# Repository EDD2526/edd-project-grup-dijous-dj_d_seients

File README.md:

View this project on [CADLAB.io](https://cadlab.io/project/30198). 

# Projecte Grup D (Dijous-tarda): Seients

>**Autors:
- Joan Martínez [@JoaanMG]
- Manel Frías [@manelfriass]
- Joan Heras [@jheraas]

>**Versió: V5.0 (final)

----------

## Objectiu

En primer lloc cal explicar que estem davant de l'elaboració d’un mòdul crític per a la seguretat i el funcionament del vehicle. El sistema de SEIENTS DIGITALS és la interfície entre l'energia del cotxe i la seguretat del conductor.
Per tant ens basarem en aquests puts adjuntats al guió:

  a) 3 motors (posició, alçada, reclinació) amb els seus finals de carrera.
  b) Calefacció del seient. 
  c) Sensor digital de cinturons.
  d) Memòria externa no volàtil per guardar posicions pre-programades.

>PCB per ...

L'objectiu principal és dissenyar i fabricar una PCB funcional per a la gestió del subsistema de seients elèctrics d'un vehicle, complint els següents punts:

- Controlar 3 motors del seient:
- Posició longitudinal, alçada, Inclinació del respatller
- Detectar finals de carrera per evitar sobrecàrregues mecàniques.
- Implementar calefacció del seient amb control electrònic.
- Detectar estat del cinturó de seguretat.
- Guardar i recuperar posicions programades del seient mitjançant memòria no volàtil.
- Permetre la interacció de l’usuari amb botonera.
- Comunicar-se amb la xarxa del vehicle via bus CAN.
- Permetre monitorització i debug via USART.

## Diagrama de blocs

### Descripció/funcionalitat de cada bloc

  - ALIMENTACIÓ: El sistema s’alimenta a partir de la bateria del vehicle (12V). Aquesta tensió es condiciona mitjançant dues etapes. Això permet alimentar:

    * Microcontrolador.
    * Sensors.
    * Comunicacions.
 
  - UART: per debug i monitorització.

  - MICROCONTROLADOR: És el nucli del sistema, encarregat de: Processar les entrades (botons i sensors), controlar els motors, gestionar la comunicació amb altres mòduls. També gestiona diferents interfícies:

    * GPIO → botonera i sensors.
    * PWM → control de motors i calefacció.
    * I2C → memòria i sensor de temperatura.
    * CAN → comunicació amb el vehicle.
    * UART → debug.

  - BOTONERA: Permet a l’usuari controlar el seient:

    * Posició.
    * Alçada.
    * Reclinació.
    
  - SENSORS: de temperatura i cinturons.

  - SISTEMA DE MOTORS.

  - SISTEMA DE CALEFACCIÓ.

  - MEMÒRIA.

  - COMUNICACIÓNS.

-----------

## Requisits / Especificacions

  * Alimentació; 12V, regulada 5V
  * Microcontrolador PIC18xxxxxxxxx
  * ...

-----------

## Components

| Descripci&#243; | Ref | Package |Datasheet | Prove&#239;dor | Value | Preu | Unitats |

| Capacitor | KAF21BR71H104JM | SMD | [Enllaç](https://www.mouser.com/datasheet/3/5926/1/AutoMLCCKAF.pdf) | 100 nF| 0,078 € | x21 |

| Capacitor | KAF21BR71H104JM | SMD | [Enllaç](https://www.mouser.com/datasheet/3/5926/1/AutoMLCCKAF.pdf) | 220 uF| 0,078 € | x2 |

| Capacitor | KAF21BR71H104JM | SMD | [Enllaç](https://www.mouser.com/datasheet/3/5926/1/AutoMLCCKAF.pdf) | 10 uF| 0,078 € | x2 |

| Capacitor | KAF21BR71H104JM | THT | [Enllaç](https://www.mouser.com/datasheet/3/5926/1/AutoMLCCKAF.pdf) | 100 nF| 0,078 € | x2 |

| Capacitor | KAF21BR71H104JM | THT | [Enllaç](https://www.mouser.com/datasheet/3/5926/1/AutoMLCCKAF.pdf) | 100 nF| 0,078 € | x2 |

| Capacitor | KAF21BR71H104JM | SMD | [Enllaç](https://www.mouser.com/datasheet/3/5926/1/AutoMLCCKAF.pdf) | 0.1 uF| 0,078 € | x3 |

| --- | --- | --- | --- | ---| --- | --- |

| Exemple | XYZ1234 | SOT-23 | [Enllaç](https://...) | DigiKey | 2 |

 | Microcontrolador | PIC18F26Q83-I/SS | SOIC-28 |[Datasheet](https://www.mouser.es/datasheet/2/268/PIC18F27_47_57Q83_Preliminary_Data_Sheet_40002265B-2887591.pdf) | [Mouser](https://www.mouser.es/c/?q=PIC18F27Q83-I%2FSO)| 2,17&euro;| 1x |
| XTAL-Ressonador | CSTCR7M99G53-R0 | SMD |[Datasheet](https://www.mouser.es/datasheet/2/281/p16e-522700.pdf) | [Mouser](https://www.mouser.es/ProductDetail/Murata-Electronics/CSTCR7M99G53-R0?qs=Zd9RUO93%2Fo7cnwzsujIkpA%3D%3D)  | 0,27&euro; | 1x |

-----------

## Software

### Eines:

  * KiCad 9.0 o superior
  * 

### Configuraci&#243; :

  * 

### Funcionalitats:

  - Controlar 3 motors del seient:
  - Posició longitudinal, alçada, Inclinació del respatller
  - Detectar finals de carrera per evitar sobrecàrregues mecàniques.
  - Implementar calefacció del seient amb control electrònic.
  - Detectar estat del cinturó de seguretat.
  - Guardar i recuperar posicions programades del seient mitjançant memòria no volàtil.
  - Permetre la interacció de l’usuari amb botonera.
  - Comunicar-se amb la xarxa del vehicle via bus CAN.
  - Permetre monitorització i debug via USART

-----------

## Historial de canvis:

23/03/2026 a les 14:07
Al dia d'avui s'ha modificat el diagrama de blocs: hem ajustat petites coses per finalitzar el diagrama de blocs definitiu.

23/03/2026 a les 17:22
Tan bon punt hem modificat el digrama de blocs, al dia d'avui també s'ha modificat la part sensors: hem incorporat l'esquemàtic preliminar una vegada ajustat el diagrama de blocs. Incorporats el TMP102 (sensor de temperatura) i el Hall A3144 (sensor digital dels cinturons).

24/03/2026 a les 14:07
Al dia d'avui s'ha modificat la part d'alimentació: hem incorporat dues coses importants: FUSIBLE i DIODES TVS. Hem modificat els possibles errors mitjançant una escombrada de l'ERC. Alimentació (ACABAT AL 100%).

24/03/2026 a les 18:48
S'ha modificat la part de SENSORS: una vegada incorporats el TMP102 (sensor de temperatura) i el Hall A3144 (sensor digital dels cinturons) hem realitzat la incorporación dels components: resistències pull-up, capacitats de desacoblament, ...

25/03/2026 a les 09:35
Al dia d'avui s'ha modificat la part de sensors: hem incorporat etiquetes i hem modificat algunes connexions degut a problemes amb l'ERC, SENSORS (ACABAT AL 100%).

25/03/2026 a les 1O:07
S'ha modificat la part de SENSORS: hem finalitzat tot l'esquemàtic d'aquesta part i donem per acabada la part de SENSORS.

25/03/2026 a les 09:35
Efectuada la simulació per demostrar el funcionamenten del LM1117-3.3 (part d'ALIMENTACIÓ) a LTSpice.

| Data | Autor     | Branch | Versi&#243; | Descripci&#243; |
| --- | --- | --- | --- | --- |
|  28/03/2023 | mlopez | Master | initial commit | Primera versi&#243; d'esquem&#224;tic i selecci&#243; de components |
E s t a   e s   u n a   l   n e a   d e   p r u e b a   p a r a   e l   r e p o s i t o r i o

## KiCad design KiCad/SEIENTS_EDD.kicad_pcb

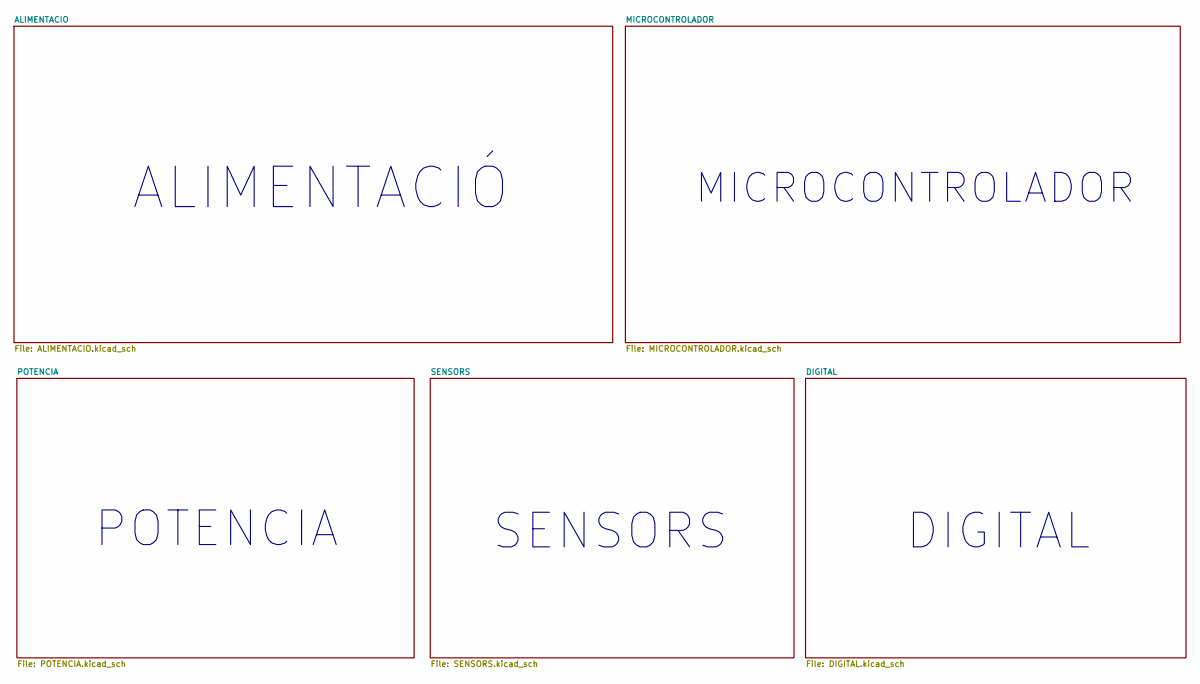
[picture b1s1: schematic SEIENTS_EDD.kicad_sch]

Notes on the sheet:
SENSORS
DIGITAL
POTENCIA
ALIMENTACIÓ
MICROCONTROLADOR

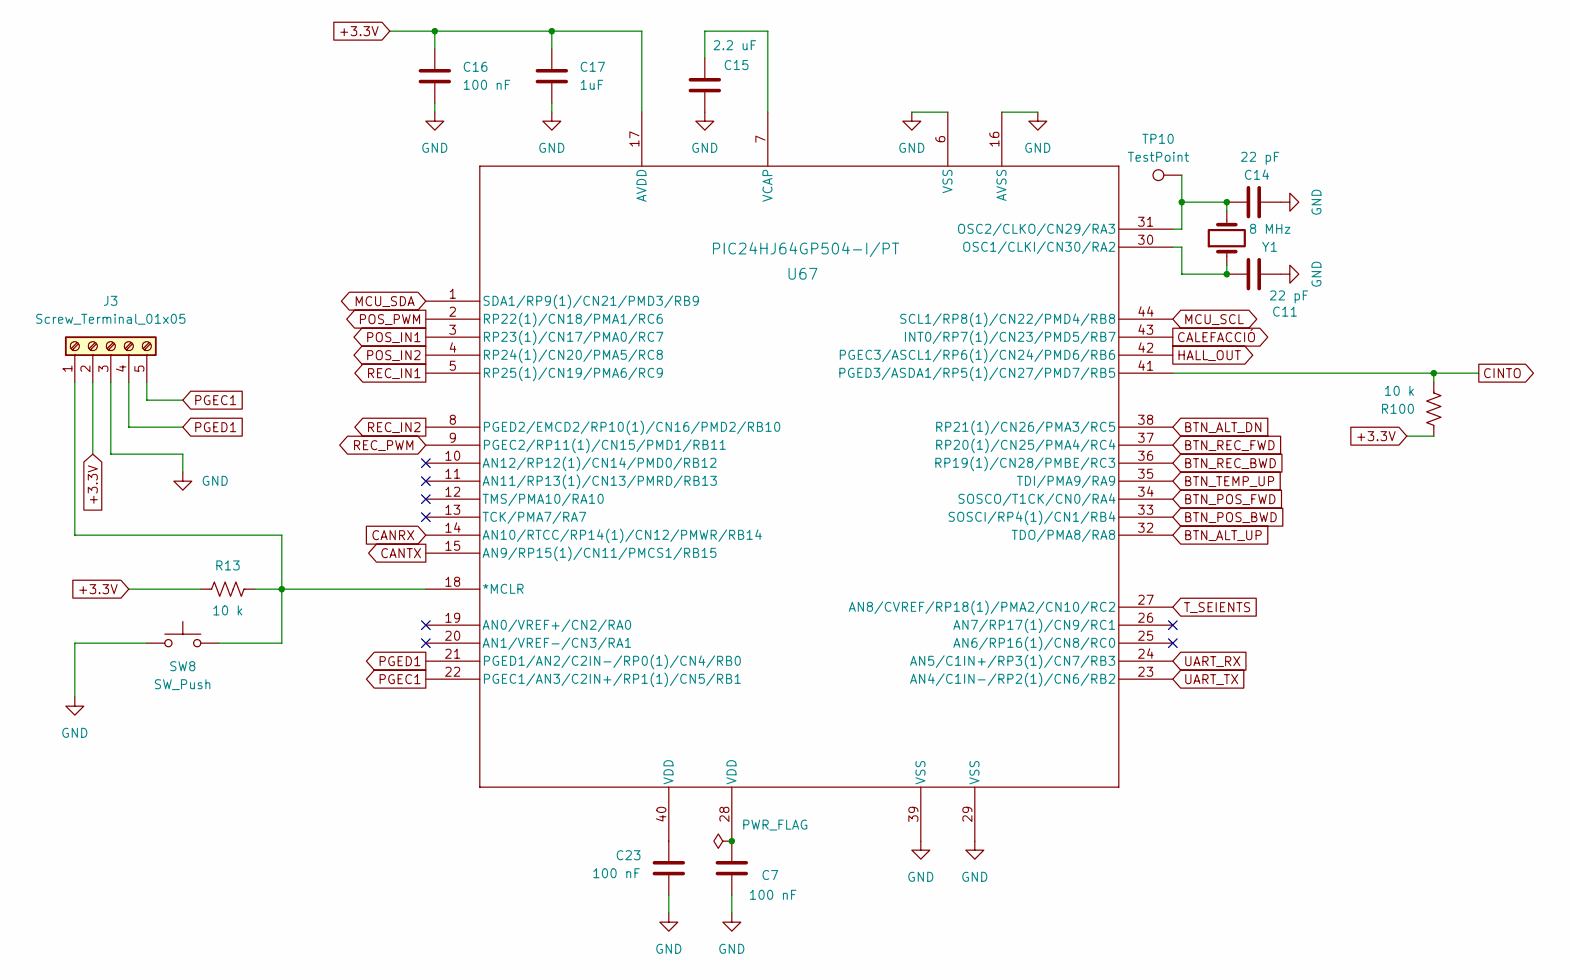
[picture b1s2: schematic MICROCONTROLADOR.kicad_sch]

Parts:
C7, C16, C23: 100 nF; C_0805_2012Metric
C11, C14: 22 pF; C_0805_2012Metric
C15: 2.2 uF; C_0805_2012Metric
C17: 1uF; C_0805_2012Metric
J3: Screw_Terminal_01x05; TerminalBlock_Phoenix_MKDS-1,5-5-5.08_1x05_P5.08mm_Horizont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
R13, R100: 10 k; R_0805_2012Metric
SW8: SW_Push; SW_Push_SPST_NO_Alps_SKRK
TP10: TestPoint; TestPoint_Pad_D1.0mm
U67: PIC24HJ64GP504-I/PT; TQFP44_10x10MC_MCH-L
Y1: 8 MHz; Crystal_HC49-4H_Vertical

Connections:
+3.3V: C16.1, C17.1, J3.2, R13.1, R100.2, U67.17 (AVDD); also elsewhere on the board
BTN_ALT_DN: U67.38 (RP21(1)/CN26/PMA3/RC5); also elsewhere on the board
BTN_ALT_UP: U67.32 (TDO/PMA8/RA8); also elsewhere on the board
BTN_POS_BWD: U67.33 (SOSCI/RP4(1)/CN1/RB4); also elsewhere on the board
BTN_POS_FWD: U67.34 (SOSCO/T1CK/CN0/RA4); also elsewhere on the board
BTN_REC_BWD: U67.36 (RP19(1)/CN28/PMBE/RC3); also elsewhere on the board
BTN_REC_FWD: U67.37 (RP20(1)/CN25/PMA4/RC4); also elsewhere on the board
BTN_TEMP_UP: U67.35 (TDI/PMA9/RA9); also elsewhere on the board
CALEFACCIÓ: U67.43 (INT0/RP7(1)/CN23/PMD5/RB7); also elsewhere on the board
CANRX: U67.14 (AN10/RTCC/RP14(1)/CN12/PMWR/RB14); also elsewhere on the board
CANTX: U67.15 (AN9/RP15(1)/CN11/PMCS1/RB15); also elsewhere on the board
CINTO: R100.1, U67.41 (PGED3/ASDA1/RP5(1)/CN27/PMD7/RB5); also elsewhere on the board
GND: C7.2, C11.2, C14.2, C15.1, C16.2, C17.2, C23.2, J3.3, SW8.1, U67.6 (VSS), U67.16 (AVSS), U67.29 (VSS), U67.39 (VSS); also elsewhere on the board
HALL_OUT: U67.42 (PGEC3/ASCL1/RP6(1)/CN24/PMD6/RB6); also elsewhere on the board
MCU_SCL: U67.44 (SCL1/RP8(1)/CN22/PMD4/RB8); also elsewhere on the board
MCU_SDA: U67.1 (SDA1/RP9(1)/CN21/PMD3/RB9); also elsewhere on the board
unnamed: C7.1, U67.28 (VDD)
unnamed: C23.1, U67.40 (VDD)
unnamed: J3.1, R13.2, SW8.2, U67.18 (*MCLR)
unnamed: C11.1, U67.30 (OSC1/CLKI/CN30/RA2), Y1.1
unnamed: C14.1, TP10.1, U67.31 (OSC2/CLKO/CN29/RA3), Y1.2
unnamed: C15.2, U67.7 (VCAP)
PGEC1: J3.5, U67.22 (PGEC1/AN3/C2IN+/RP1(1)/CN5/RB1)
PGED1: J3.4, U67.21 (PGED1/AN2/C2IN-/RP0(1)/CN4/RB0)
POS_IN1: U67.3 (RP23(1)/CN17/PMA0/RC7); also elsewhere on the board
POS_IN2: U67.4 (RP24(1)/CN20/PMA5/RC8); also elsewhere on the board
POS_PWM: U67.2 (RP22(1)/CN18/PMA1/RC6); also elsewhere on the board
REC_IN1: U67.5 (RP25(1)/CN19/PMA6/RC9); also elsewhere on the board
REC_IN2: U67.8 (PGED2/EMCD2/RP10(1)/CN16/PMD2/RB10); also elsewhere on the board
REC_PWM: U67.9 (PGEC2/RP11(1)/CN15/PMD1/RB11); also elsewhere on the board
T_SEIENTS: U67.27 (AN8/CVREF/RP18(1)/PMA2/CN10/RC2); also elsewhere on the board
UART_RX: U67.24 (AN5/C1IN+/RP3(1)/CN7/RB3); also elsewhere on the board
UART_TX: U67.23 (AN4/C1IN-/RP2(1)/CN6/RB2); also elsewhere on the board

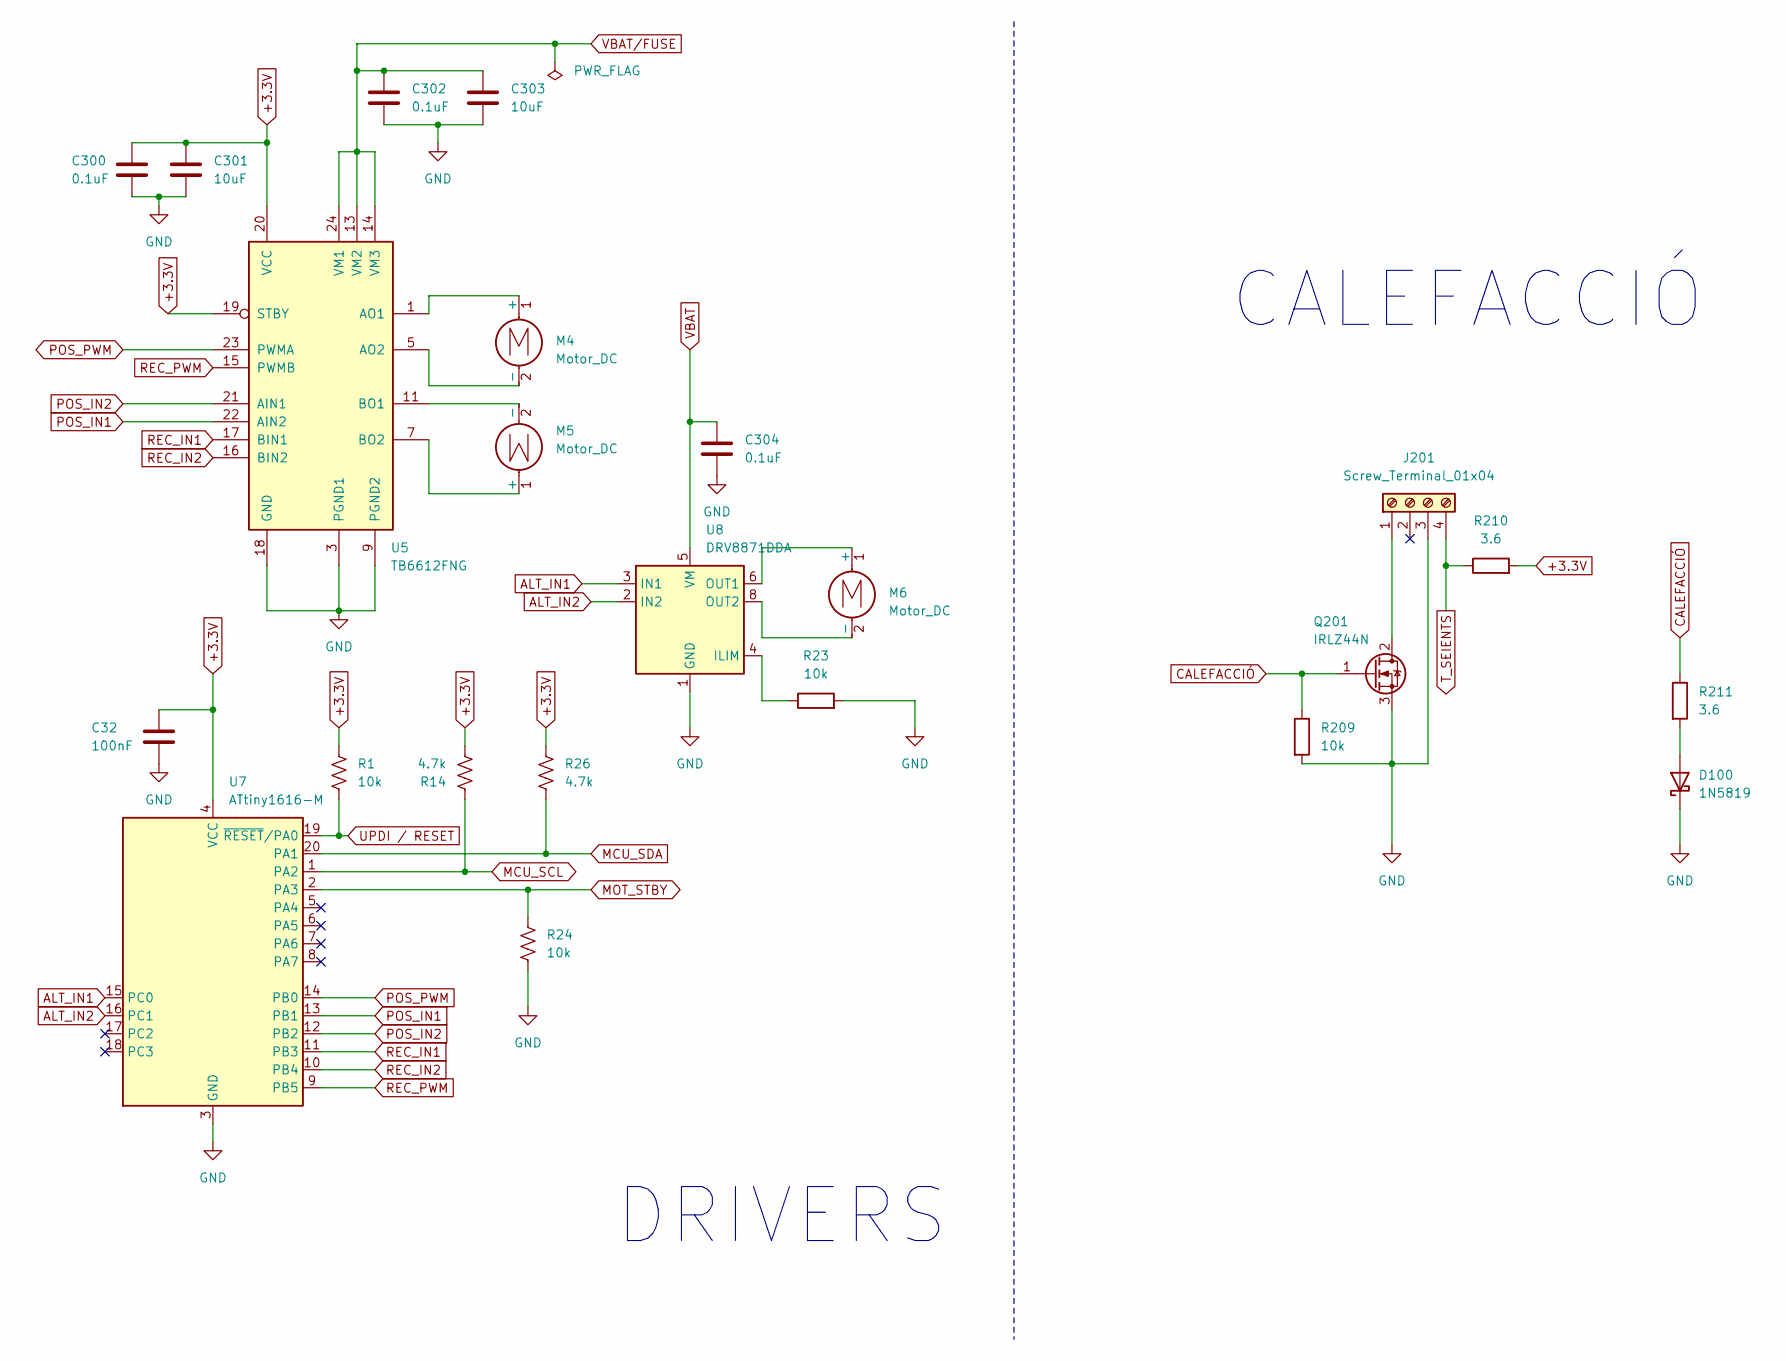
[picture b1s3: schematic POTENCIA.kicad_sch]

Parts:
C32: 100nF; C_0805_2012Metric
C300, C302, C304: 0.1uF; C_0805_2012Metric
C301, C303: 10uF; CP_Radial_D5.0mm_P2.50mm
D100: 1N5819; D_DO-41_SOD81_P10.16mm_Horizontal
J201: Screw_Terminal_01x04; TerminalBlock_Phoenix_MKDS-1,5-4-5.08_1x04_P5.08mm_Horizont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
M4, M5, M6: Motor_DC; TerminalBlock_Phoenix_MKDS-1,5-2-5.08_1x02_P5.08mm_Horizont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
Q201: IRLZ44N; TO-220-3_Vertical
R1, R23, R24, R209: 10k; R_0805_2012Metric
R14, R26: 4.7k; R_0805_2012Metric
R210, R211: 3.6; R_0805_2012Metric
U5: TB6612FNG; SSOP-24_5.3x8.2mm_P0.65mm
U7: ATtiny1616-M; VQFN-20-1EP_3x3mm_P0.4mm_EP1.7x1.7mm
U8: DRV8871DDA; Texas_HTSOP-8-1EP_3.9x4.9mm_P1.27mm_EP2.95x4.9mm_Mask2.4x3.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

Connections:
+3.3V: C32.1, C300.1, C301.1, R1.1, R14.2, R26.1, R210.2, U5.19 (STBY), U5.20 (VCC), U7.4 (VCC); also elsewhere on the board
ALT_IN1: U7.15 (PC0), U8.3 (IN1)
ALT_IN2: U7.16 (PC1), U8.2 (IN2)
CALEFACCIÓ: Q201.1 (G), R209.1, R211.1; also elsewhere on the board
GND: C32.2, C300.2, C301.2, C302.2, C303.2, C304.2, D100.1 (K), J201.3, Q201.3 (S), R23.2, R24.2, R209.2, U5.3 (PGND1), U5.4 (PGND1), U5.9 (PGND2), U5.10 (PGND2), U5.18 (GND), U7.3 (GND), U7.21 (GND), U8.1 (GND), U8.7 (GND), U8.9 (GND); also elsewhere on the board
MCU_SCL: R14.1, U7.1 (PA2); also elsewhere on the board
MCU_SDA: R26.2, U7.20 (PA1); also elsewhere on the board
MOT_STBY: R24.1, U7.2 (PA3)
unnamed: D100.2 (A), R211.2
unnamed: J201.1, Q201.2 (D)
unnamed: M4.1 (+), U5.1 (AO1), U5.2 (AO1)
unnamed: M4.2 (-), U5.5 (AO2), U5.6 (AO2)
unnamed: M5.1 (+), U5.7 (BO2), U5.8 (BO2)
unnamed: M5.2 (-), U5.11 (BO1), U5.12 (BO1)
unnamed: M6.1 (+), U8.6 (OUT1)
unnamed: M6.2 (-), U8.8 (OUT2)
unnamed: R23.1, U8.4 (ILIM)
POS_IN1: U5.22 (AIN2), U7.13 (PB1); also elsewhere on the board
POS_IN2: U5.21 (AIN1), U7.12 (PB2); also elsewhere on the board
POS_PWM: U5.23 (PWMA), U7.14 (PB0); also elsewhere on the board
REC_IN1: U5.17 (BIN1), U7.11 (PB3); also elsewhere on the board
REC_IN2: U5.16 (BIN2), U7.10 (PB4); also elsewhere on the board
REC_PWM: U5.15 (PWMB), U7.9 (PB5); also elsewhere on the board
T_SEIENTS: J201.4, R210.1; also elsewhere on the board
UPDI / RESET: R1.2, U7.19 (~RESET/PA0)
VBAT: C304.1, U8.5 (VM); also elsewhere on the board
VBAT/FUSE: C302.1, C303.1, U5.13 (VM2), U5.14 (VM3), U5.24 (VM1); also elsewhere on the board

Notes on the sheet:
CALEFACCIÓ
DRIVERS

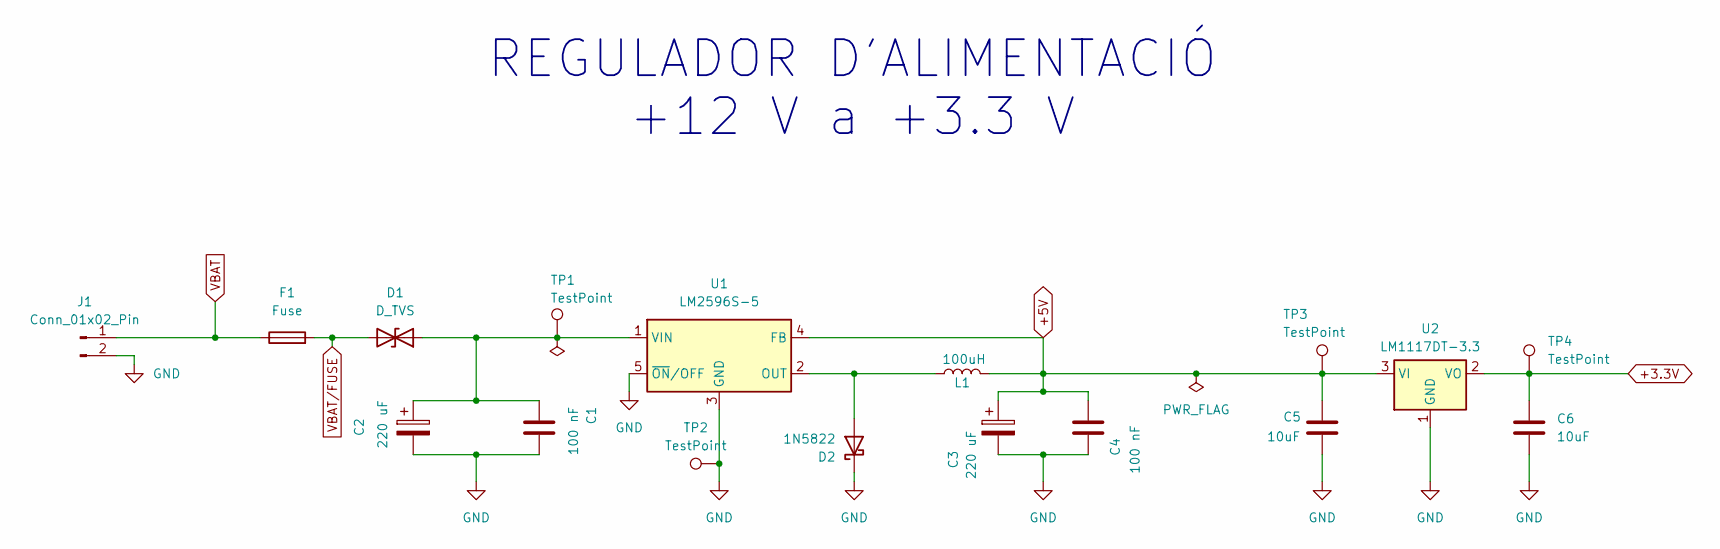
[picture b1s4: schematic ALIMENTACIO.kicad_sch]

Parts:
C1, C4: 100 nF; C_0805_2012Metric
C2, C3: 220 uF; C_0805_2012Metric
C5, C6: 10uF; C_0805_2012Metric
D1: D_TVS; D_SMA
D2: 1N5822; D_DO-201AD_P15.24mm_Horizontal
F1: Fuse; Fuseholder_Cylinder-5x20mm_Schurter_0031_8201_Horizontal_Op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
J1: Conn_01x02_Pin; TerminalBlock_Phoenix_MKDS-1,5-2-5.08_1x02_P5.08mm_Horizont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
L1: 100uH; L_Radial_D10.0mm_P5.00mm_Fastron_07M
TP1, TP2, TP3, TP4: TestPoint; TestPoint_Pad_D1.0mm
U1: LM2596S-5; TO-263-5_TabPin3
U2: LM1117DT-3.3; TO-252-3_TabPin2

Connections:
+3.3V: C6.1, TP4.1, U2.2 (VO); also elsewhere on the board
+5V: C3.1, C4.1, C5.1, L1.2, TP3.1, U1.4 (FB), U2.3 (VI); also elsewhere on the board
GND: C1.1, C2.2, C3.2, C4.2, C5.2, C6.2, D2.1 (K), J1.2, TP2.1, U1.3 (GND), U1.5 (~ON/OFF), U2.1 (GND); also elsewhere on the board
unnamed: C1.2, C2.1, D1.1 (A1), TP1.1, U1.1 (VIN)
unnamed: D2.2 (A), L1.1, U1.2 (OUT)
VBAT: F1.1, J1.1; also elsewhere on the board
VBAT/FUSE: D1.2 (A2), F1.2; also elsewhere on the board

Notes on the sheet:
REGULADOR D'ALIMENTACIÓ +12 V a +3.3 V

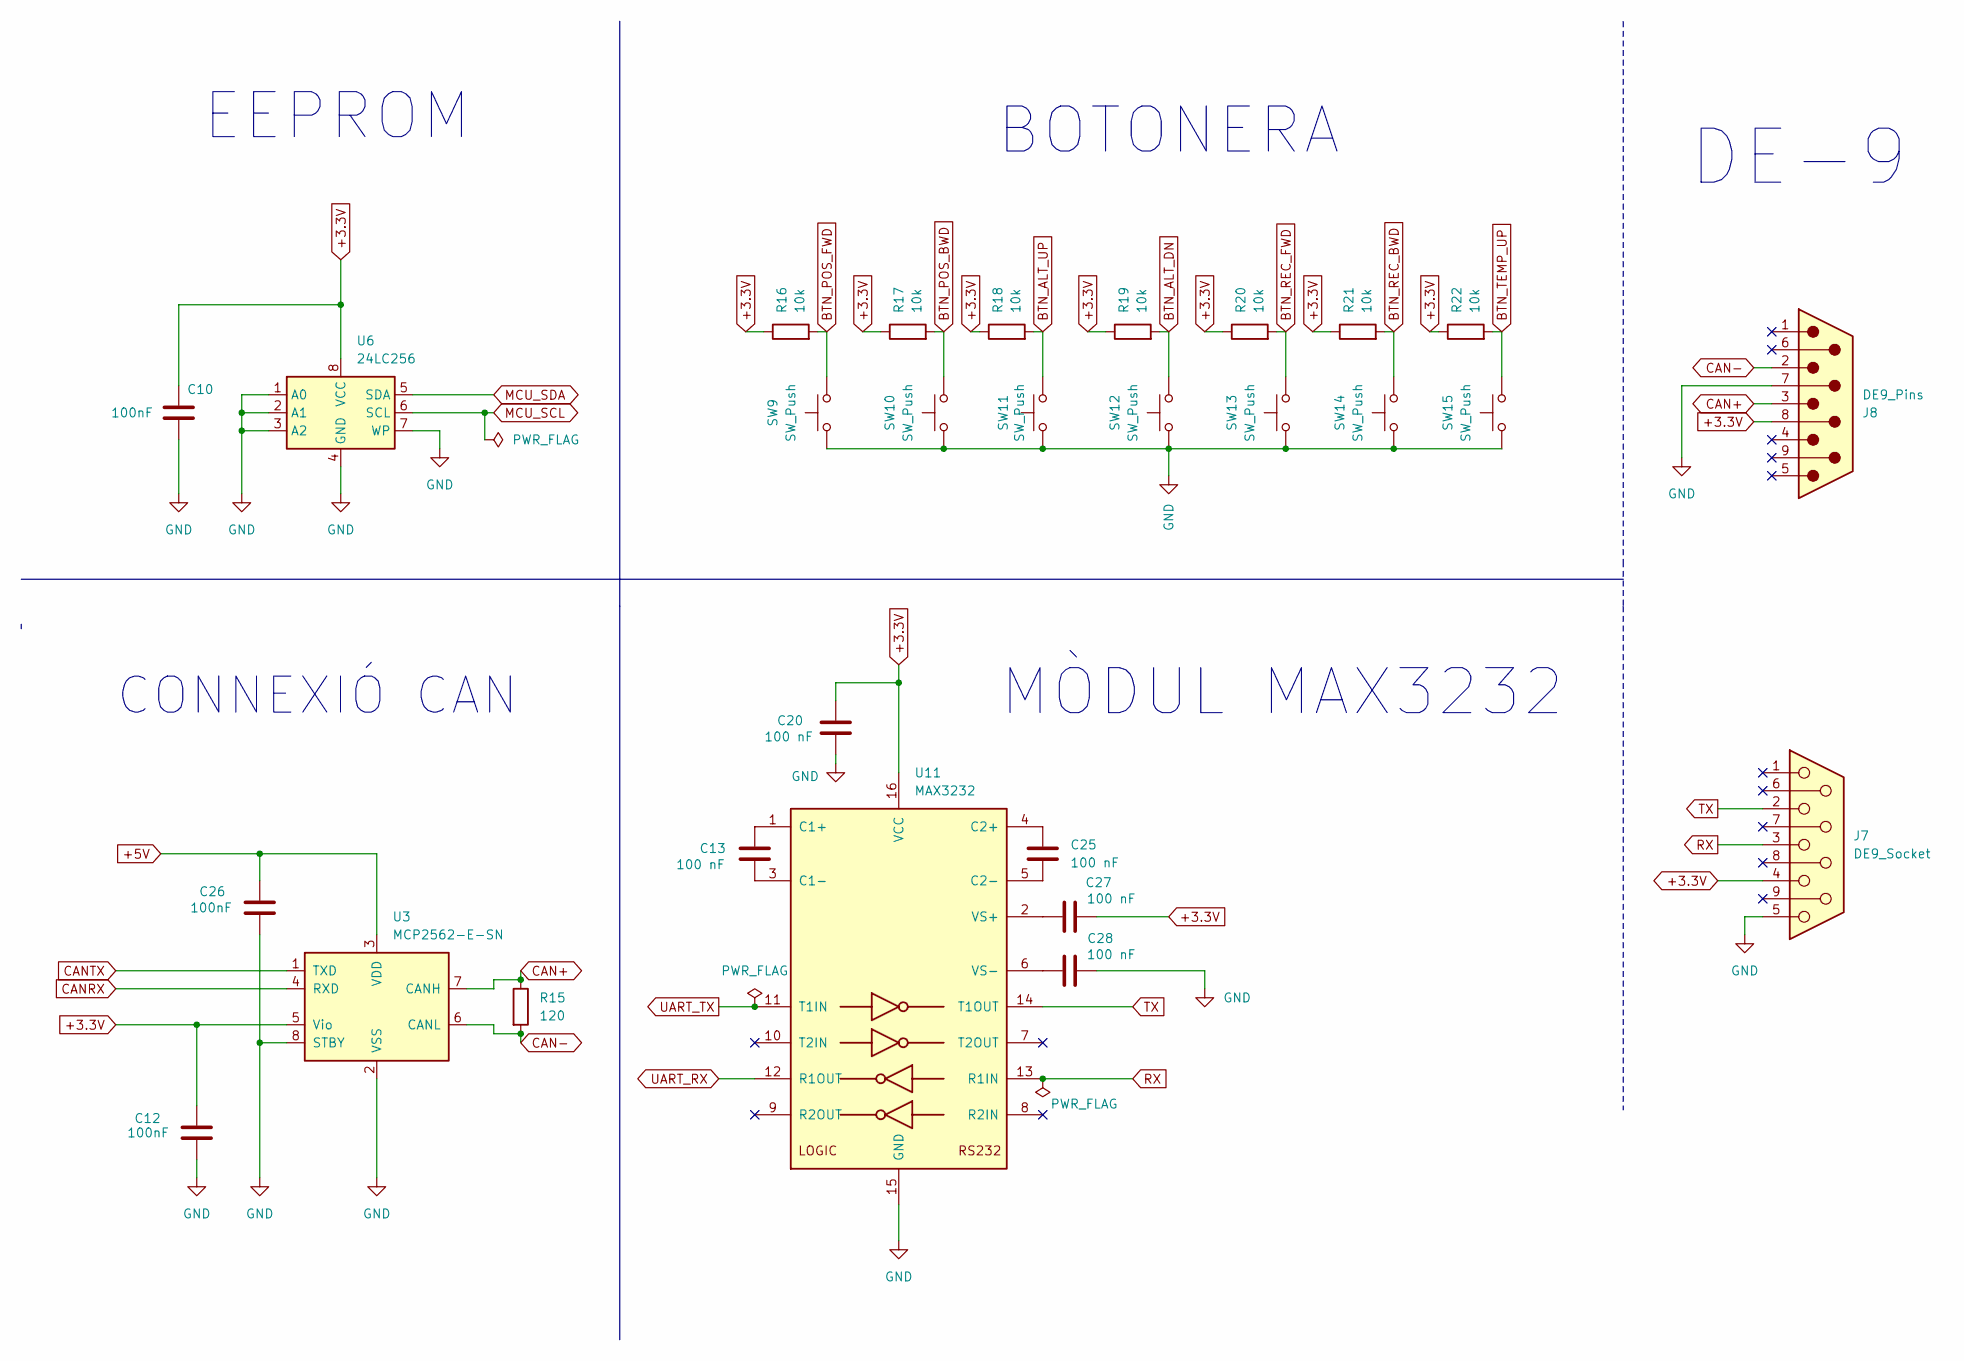
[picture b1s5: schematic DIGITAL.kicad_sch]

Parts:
C10, C12, C26: 100nF; C_0805_2012Metric
C13, C20, C25, C27, C28: 100 nF; C_0805_2012Metric
J7: DE9_Socket; DSUB-9_Socket_Horizontal_P2.77x2.84mm_EdgePinOffset4.94mm_H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
J8: DE9_Pins; DSUB-9_Pins_Horizontal_P2.77x2.84mm_EdgePinOffset4.94mm_Hou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
R15: 120; R_0805_2012Metric
R16, R17, R18, R19, R20, R21, R22: 10k; R_0805_2012Metric
SW9, SW10, SW11, SW12, SW13, SW14, SW15: SW_Push; SW_Push_SPST_NO_Alps_SKRK
U3: MCP2562-E-SN; SOIC-8_3.9x4.9mm_P1.27mm
U6: 24LC256; SOIC-8_3.9x4.9mm_P1.27mm
U11: MAX3232; SOIC-16_3.9x9.9mm_P1.27mm

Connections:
+3.3V: C10.2, C12.2, C20.1, C27.2, J7.4, J8.8, R16.1, R17.1, R18.1, R19.1, R20.1, R21.1, R22.1, U3.5 (Vio), U6.8 (VCC), U11.16 (VCC); also elsewhere on the board
+5V: C26.2, U3.3 (VDD); also elsewhere on the board
BTN_ALT_DN: R19.2, SW12.2; also elsewhere on the board
BTN_ALT_UP: R18.2, SW11.2; also elsewhere on the board
BTN_POS_BWD: R17.2, SW10.2; also elsewhere on the board
BTN_POS_FWD: R16.2, SW9.2; also elsewhere on the board
BTN_REC_BWD: R21.2, SW14.2; also elsewhere on the board
BTN_REC_FWD: R20.2, SW13.2; also elsewhere on the board
BTN_TEMP_UP: R22.2, SW15.2; also elsewhere on the board
CAN+: J8.3, R15.1, U3.7 (CANH)
CAN-: J8.2, R15.2, U3.6 (CANL)
CANRX: U3.4 (RXD); also elsewhere on the board
CANTX: U3.1 (TXD); also elsewhere on the board
GND: C10.1, C12.1, C20.2, C26.1, C28.2, J7.5, J8.7, SW9.1, SW10.1, SW11.1, SW12.1, SW13.1, SW14.1, SW15.1, U3.2 (VSS), U3.8 (STBY), U6.1 (A0), U6.2 (A1), U6.3 (A2), U6.4 (GND), U6.7 (WP), U11.15 (GND); also elsewhere on the board
MCU_SCL: U6.6 (SCL); also elsewhere on the board
MCU_SDA: U6.5 (SDA); also elsewhere on the board
unnamed: C13.1, U11.1 (C1+)
unnamed: C13.2, U11.3 (C1-)
unnamed: C25.1, U11.4 (C2+)
unnamed: C25.2, U11.5 (C2-)
unnamed: C27.1, U11.2 (VS+)
unnamed: C28.1, U11.6 (VS-)
RX: J7.3, U11.13 (R1IN)
TX: J7.2, U11.14 (T1OUT)
UART_RX: U11.12 (R1OUT); also elsewhere on the board
UART_TX: U11.11 (T1IN); also elsewhere on the board

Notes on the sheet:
BOTONERA
EEPROM
MÒDUL MAX3232
DE-9
CONNEXIÓ CAN

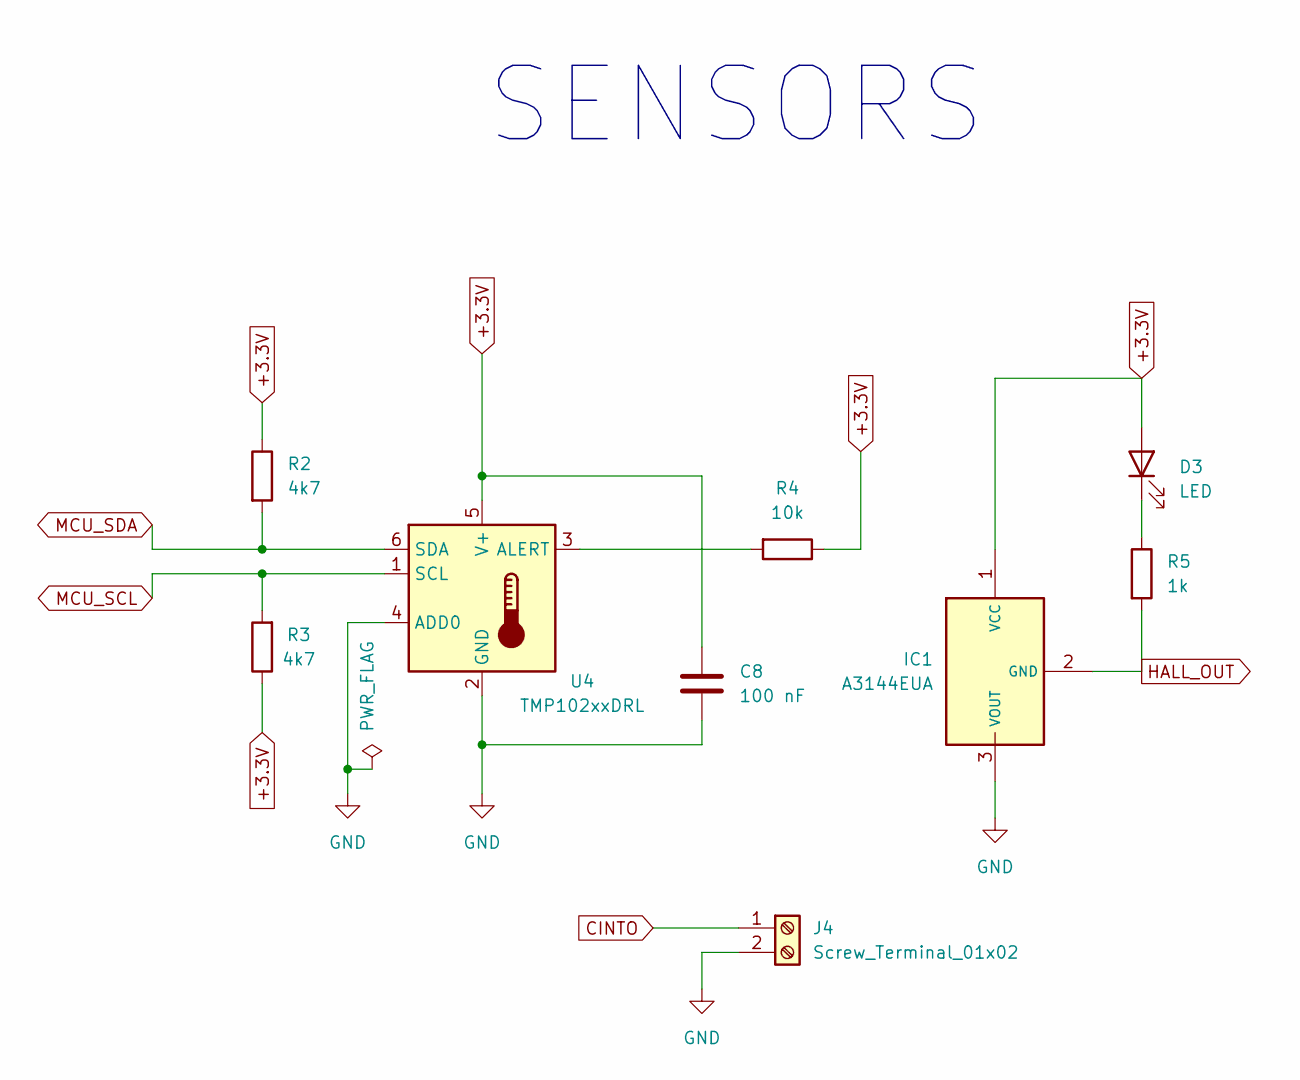
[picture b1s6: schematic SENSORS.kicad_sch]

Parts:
C8: 100 nF; C_0805_2012Metric
D3: LED; LED_D3.0mm
IC1: A3144EUA; Manufacturer_Part_Number A3144EUA
J4: Screw_Terminal_01x02; TerminalBlock_Phoenix_MKDS-1,5-2-5.08_1x02_P5.08mm_Horizont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
R2, R3: 4k7; R_0805_2012Metric
R4: 10k; R_0805_2012Metric
R5: 1k; R_0805_2012Metric
U4: TMP102xxDRL; SOT-563

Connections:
+3.3V: C8.1, D3.2 (A), IC1.1 (VCC), R2.1, R3.1, R4.1, U4.5 (V+); also elsewhere on the board
CINTO: J4.1; also elsewhere on the board
GND: C8.2, IC1.3 (VOUT), J4.2, U4.2 (GND), U4.4 (ADD0); also elsewhere on the board
HALL_OUT: IC1.2 (GND), R5.2; also elsewhere on the board
MCU_SCL: R3.2, U4.1 (SCL); also elsewhere on the board
MCU_SDA: R2.2, U4.6 (SDA); also elsewhere on the board
unnamed: D3.1 (K), R5.1
unnamed: R4.2, U4.3 (ALERT)

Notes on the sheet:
SENSORS

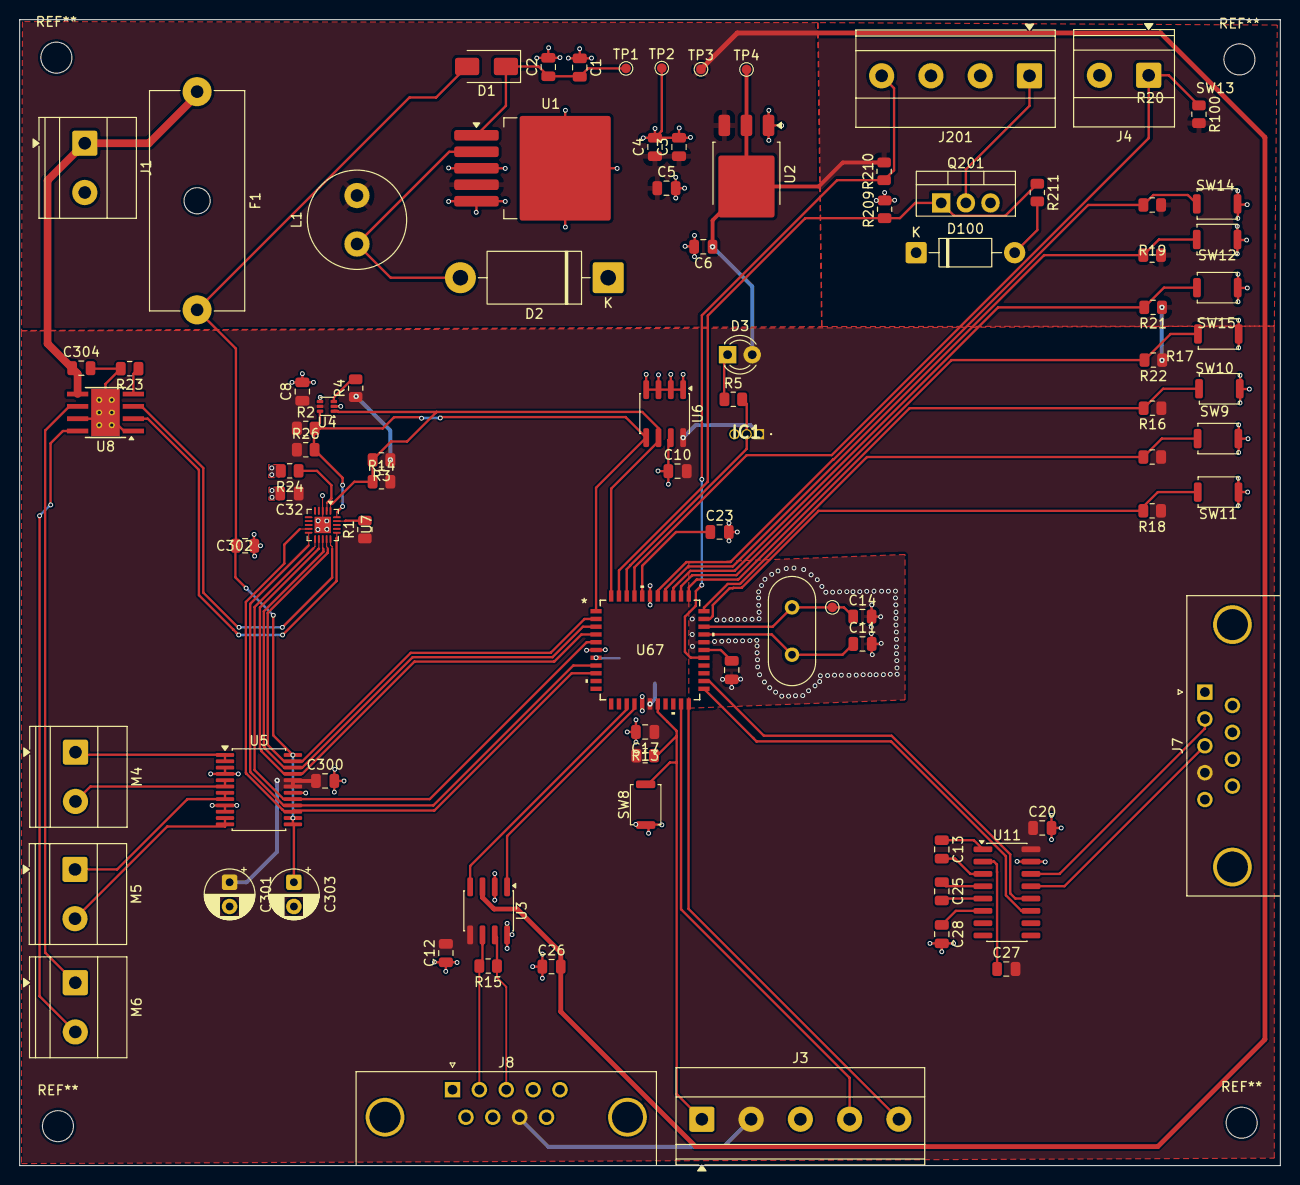
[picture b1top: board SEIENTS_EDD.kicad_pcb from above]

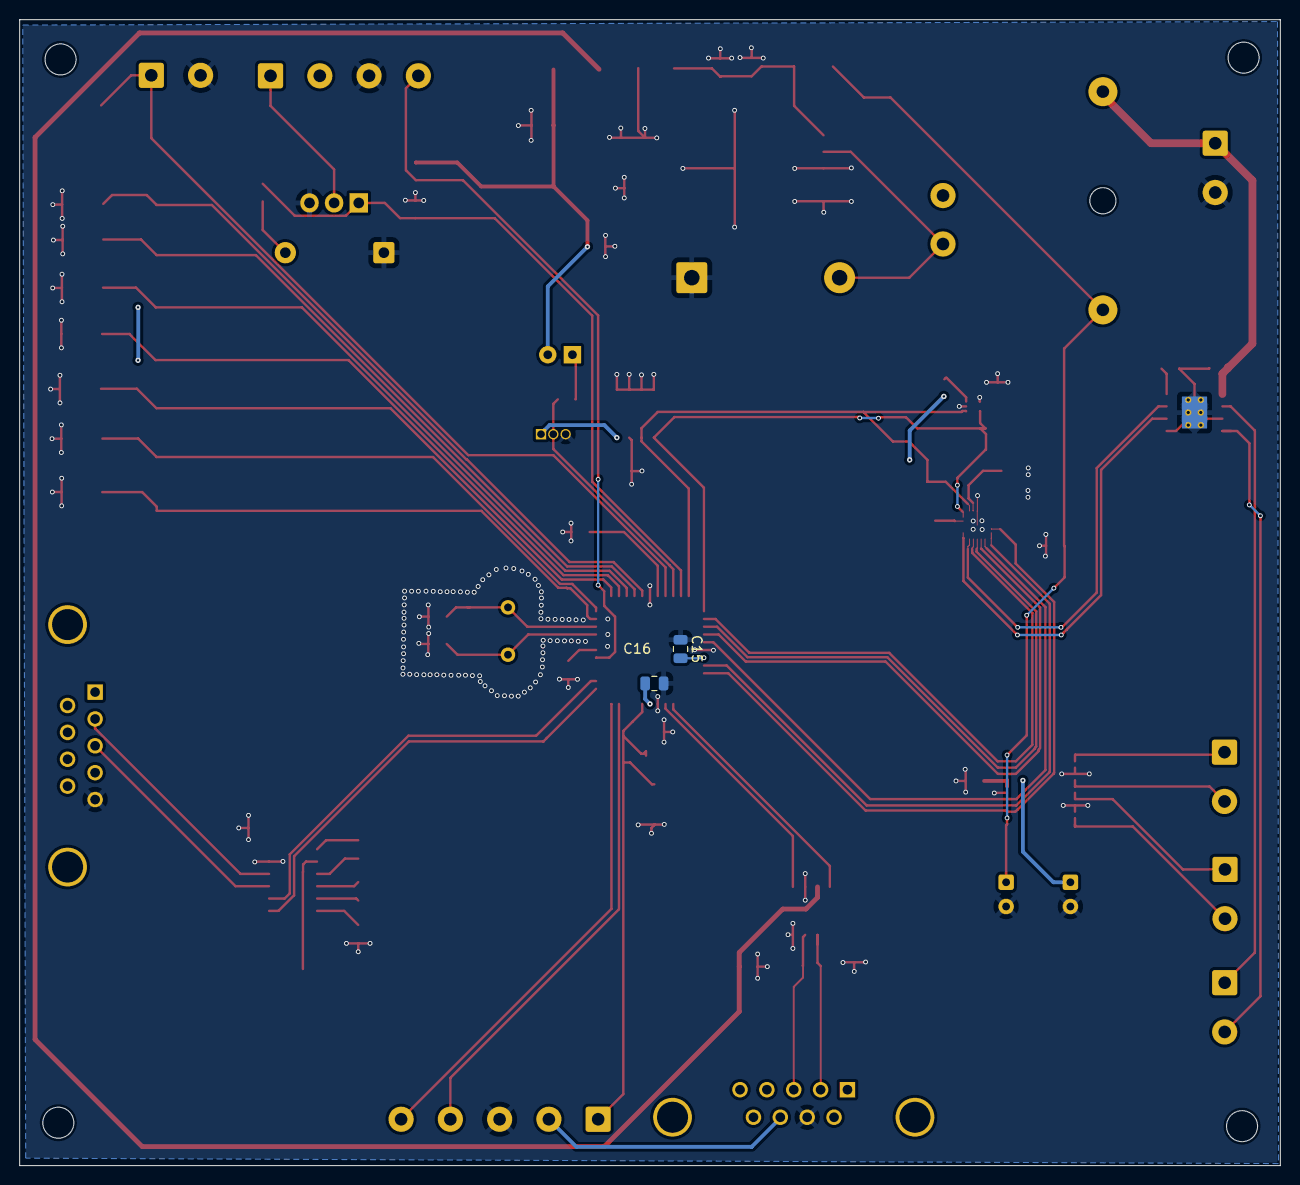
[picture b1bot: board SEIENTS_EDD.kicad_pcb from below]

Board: 2 copper layers, 130.0 x 118.2 mm, 91 parts (2 on the bottom side), 63 nets.

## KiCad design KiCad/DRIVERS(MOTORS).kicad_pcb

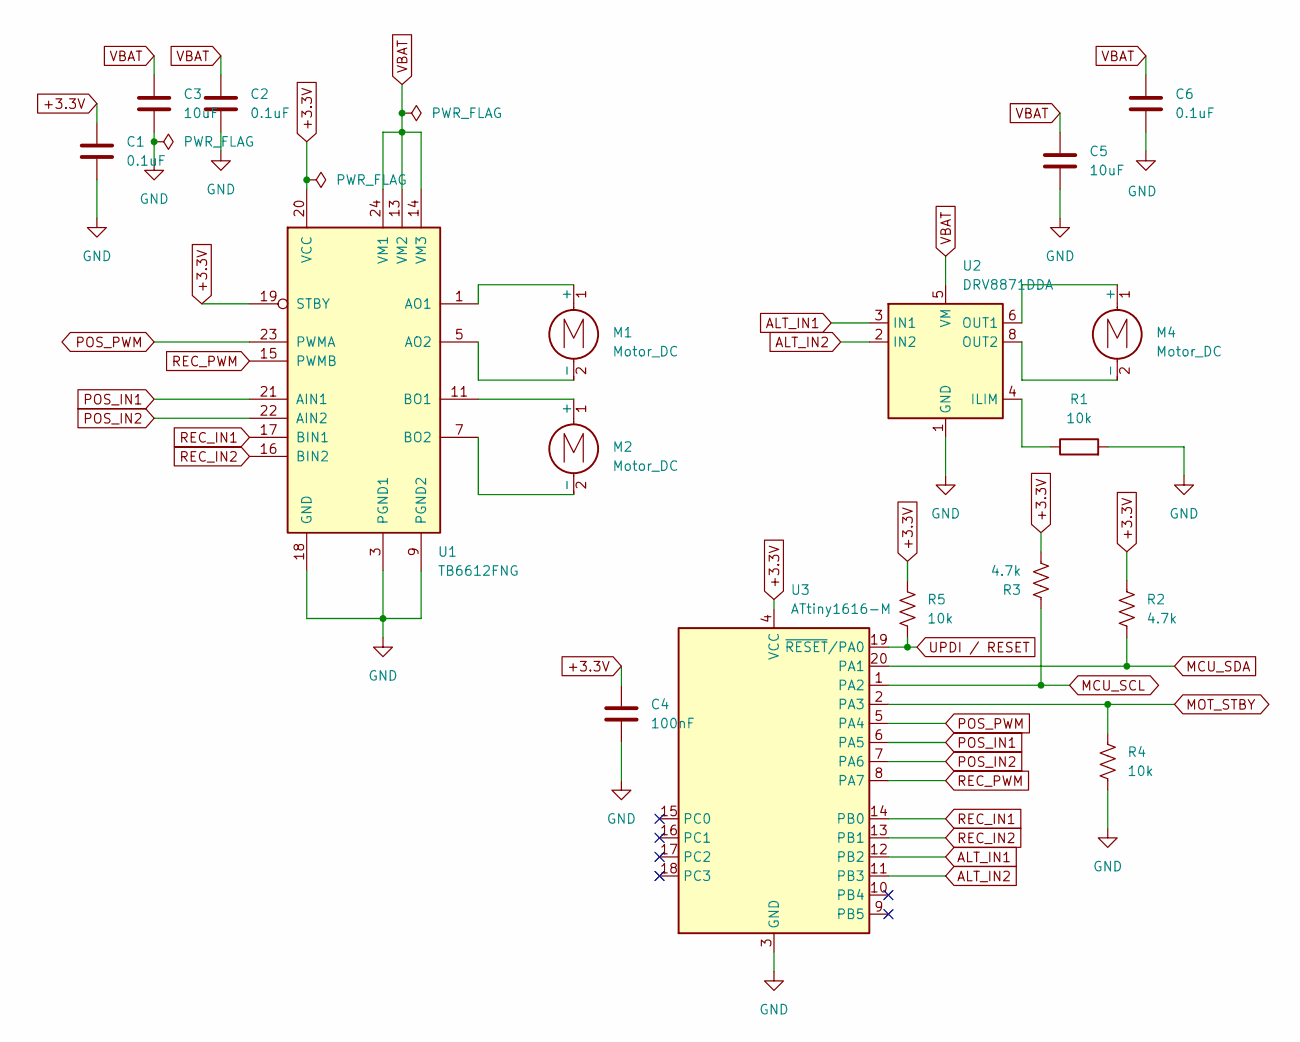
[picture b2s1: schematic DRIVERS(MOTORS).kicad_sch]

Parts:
C1, C2, C6: 0.1uF; C_0805_2012Metric
C3, C5: 10uF; CP_Radial_D5.0mm_P2.50mm
C4: 100nF; C_0805_2012Metric
M1, M2, M4: Motor_DC; PinHeader_1x02_P2.54mm_Horizontal
R1, R4, R5: 10k; R_0805_2012Metric
R2, R3: 4.7k; R_0805_2012Metric
U1: TB6612FNG; SSOP-24_5.3x8.2mm_P0.65mm
U2: DRV8871DDA; SSOP-24_5.3x8.2mm_P0.65mm
U3: ATtiny1616-M; VQFN-20-1EP_3x3mm_P0.4mm_EP1.7x1.7mm

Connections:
+3.3V: C1.1, C4.1, R2.1, R3.2, R5.1, U1.19 (STBY), U1.20 (VCC), U3.4 (VCC)
ALT_IN1: U2.3 (IN1), U3.12 (PB2)
ALT_IN2: U2.2 (IN2), U3.11 (PB3)
GND: C1.2, C2.2, C3.2, C4.2, C5.2, C6.2, R1.2, R4.2, U1.3 (PGND1), U1.4 (PGND1), U1.9 (PGND2), U1.10 (PGND2), U1.18 (GND), U2.1 (GND), U2.7 (GND), U2.9 (GND), U3.3 (GND), U3.21 (GND)
MCU_SCL: R3.1, U3.1 (PA2)
MCU_SDA: R2.2, U3.20 (PA1)
MOT_STBY: R4.1, U3.2 (PA3)
unnamed: M1.1 (+), U1.1 (AO1), U1.2 (AO1)
unnamed: M1.2 (-), U1.5 (AO2), U1.6 (AO2)
unnamed: M2.1 (+), U1.11 (BO1), U1.12 (BO1)
unnamed: M2.2 (-), U1.7 (BO2), U1.8 (BO2)
unnamed: M4.1 (+), U2.6 (OUT1)
unnamed: M4.2 (-), U2.8 (OUT2)
unnamed: R1.1, U2.4 (ILIM)
POS_IN1: U1.21 (AIN1), U3.6 (PA5)
POS_IN2: U1.22 (AIN2), U3.7 (PA6)
POS_PWM: U1.23 (PWMA), U3.5 (PA4)
REC_IN1: U1.17 (BIN1), U3.14 (PB0)
REC_IN2: U1.16 (BIN2), U3.13 (PB1)
REC_PWM: U1.15 (PWMB), U3.8 (PA7)
UPDI / RESET: R5.2, U3.19 (~RESET/PA0)
VBAT: C2.1, C3.1, C5.1, C6.1, U1.13 (VM2), U1.14 (VM3), U1.24 (VM1), U2.5 (VM)

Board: 2 copper layers, 17 parts (0 on the bottom side), 22 nets, no tracks yet.
